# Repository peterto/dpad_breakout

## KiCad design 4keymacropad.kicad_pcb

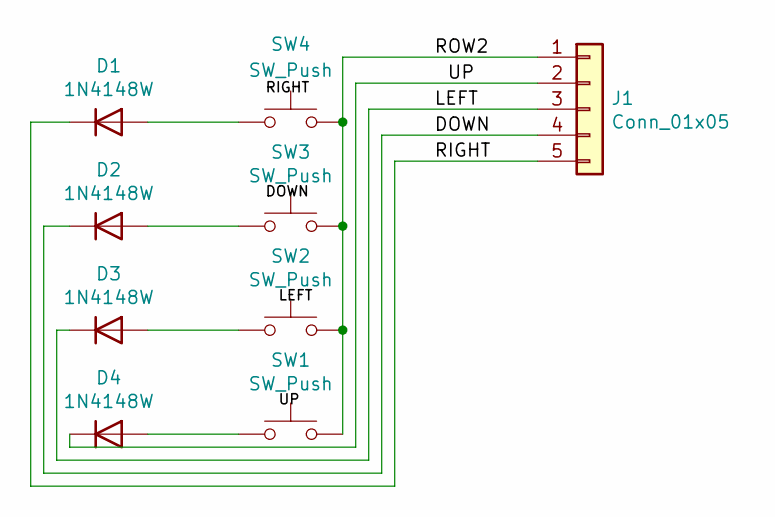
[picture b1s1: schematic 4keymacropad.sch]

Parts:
D1, D2, D3, D4: 1N4148W; D_SOD-123
J1: Conn_01x05; JST_PH_S5B-PH-K_1x05_P2.00mm_Horizontal
SW1, SW2, SW3, SW4: SW_Push; Kailh_socket_MX_optional

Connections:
/DOWN: D2.1 (K), J1.4
/LEFT: D3.1 (K), J1.3
/RIGHT: D1.1 (K), J1.5
/ROW2: J1.1, SW1.2, SW2.2, SW3.2, SW4.2
/UP: D4.1 (K), J1.2
unnamed: D1.2 (A), SW4.1
unnamed: D2.2 (A), SW3.1
unnamed: D3.2 (A), SW2.1
unnamed: D4.2 (A), SW1.1

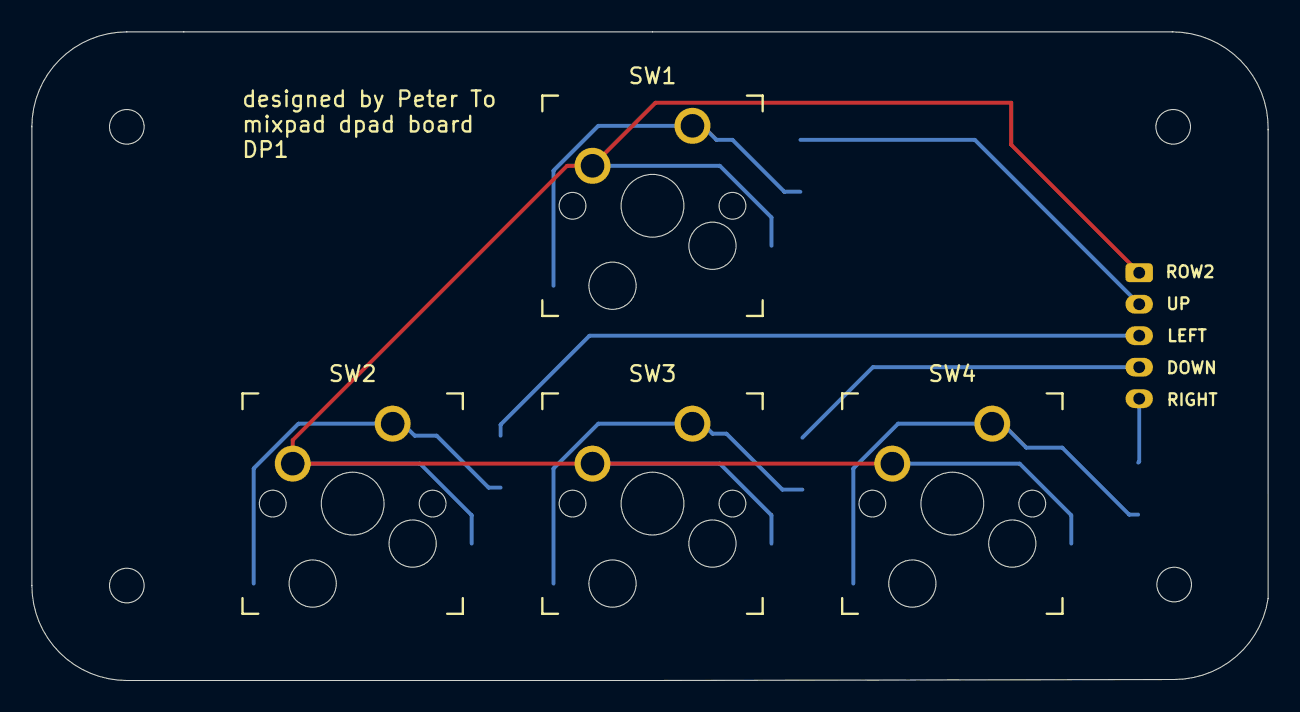
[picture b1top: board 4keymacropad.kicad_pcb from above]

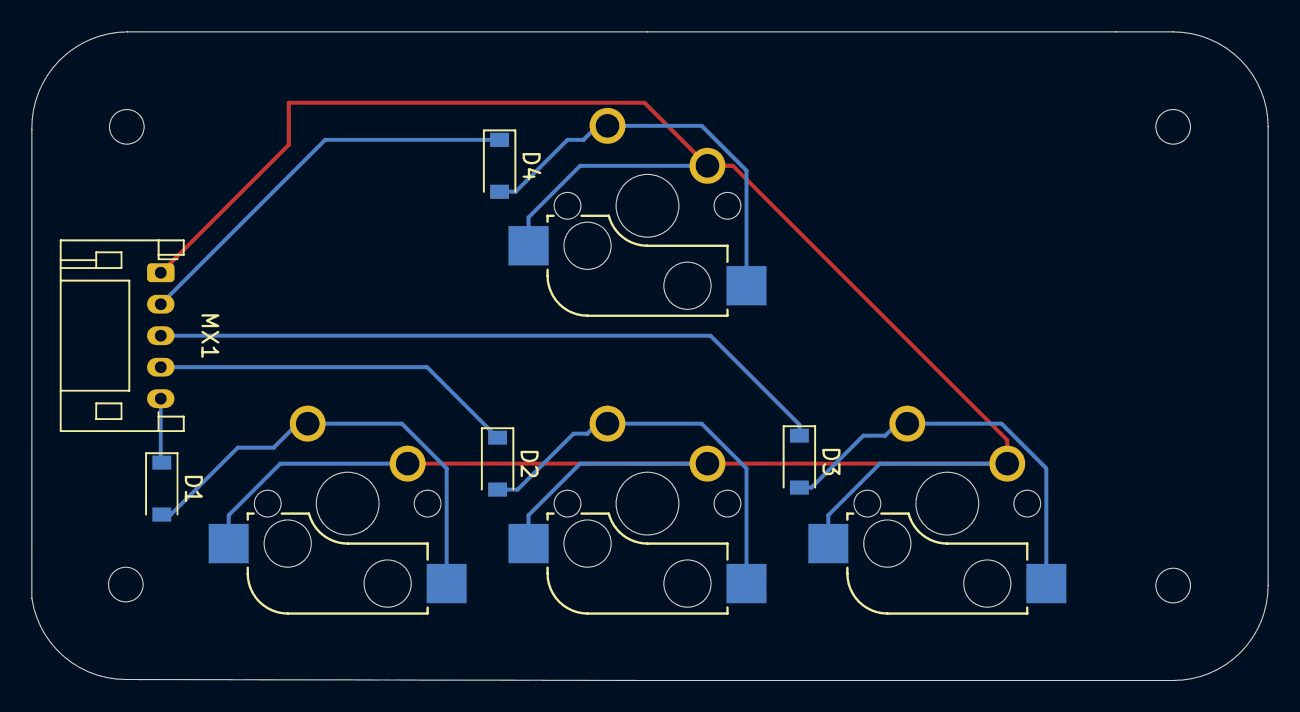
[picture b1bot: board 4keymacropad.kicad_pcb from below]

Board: 2 copper layers, 78.5 x 41.2 mm, 9 parts (5 on the bottom side), 9 nets.

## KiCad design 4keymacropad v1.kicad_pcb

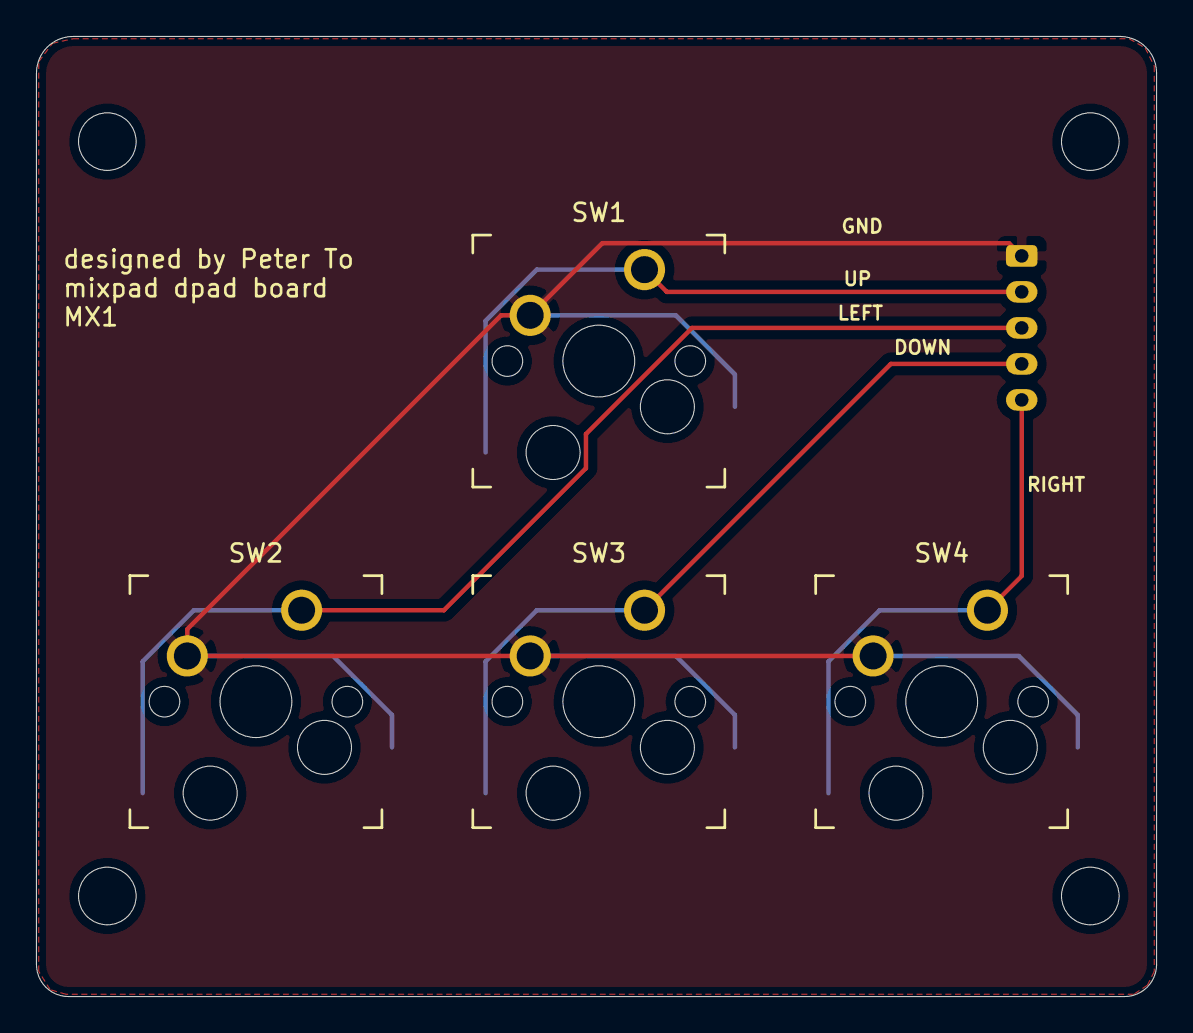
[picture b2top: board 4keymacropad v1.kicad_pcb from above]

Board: 2 copper layers, 62.2 x 53.3 mm, 5 parts (1 on the bottom side), 5 nets.

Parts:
J1: Conn_01x05; JST_PH_S5B-PH-K_1x05_P2.00mm_Horizontal
SW1, SW2, SW3, SW4: SW_Push; Kailh_socket_MX_optional

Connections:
GND: J1.1, SW1.2, SW2.2, SW3.2, SW4.2
unnamed: J1.2, SW1.1
unnamed: J1.3, SW2.1
unnamed: J1.4, SW3.1
unnamed: J1.5, SW4.1

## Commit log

2021-12-31 First version of dpad breakout
2021-12-31 version two of pcb, moves the jst ph to the center and right side of the pcb and change m3 to m2 holes, shrinks length and increases width of pcb, removes top layer ground pour
2021-12-31 Updates top right edge to match other edges, and moves ground pour to follow new edge cut
2022-01-04 Updates to use rows/columns from mainboard
2022-01-04 Removes copper pours
